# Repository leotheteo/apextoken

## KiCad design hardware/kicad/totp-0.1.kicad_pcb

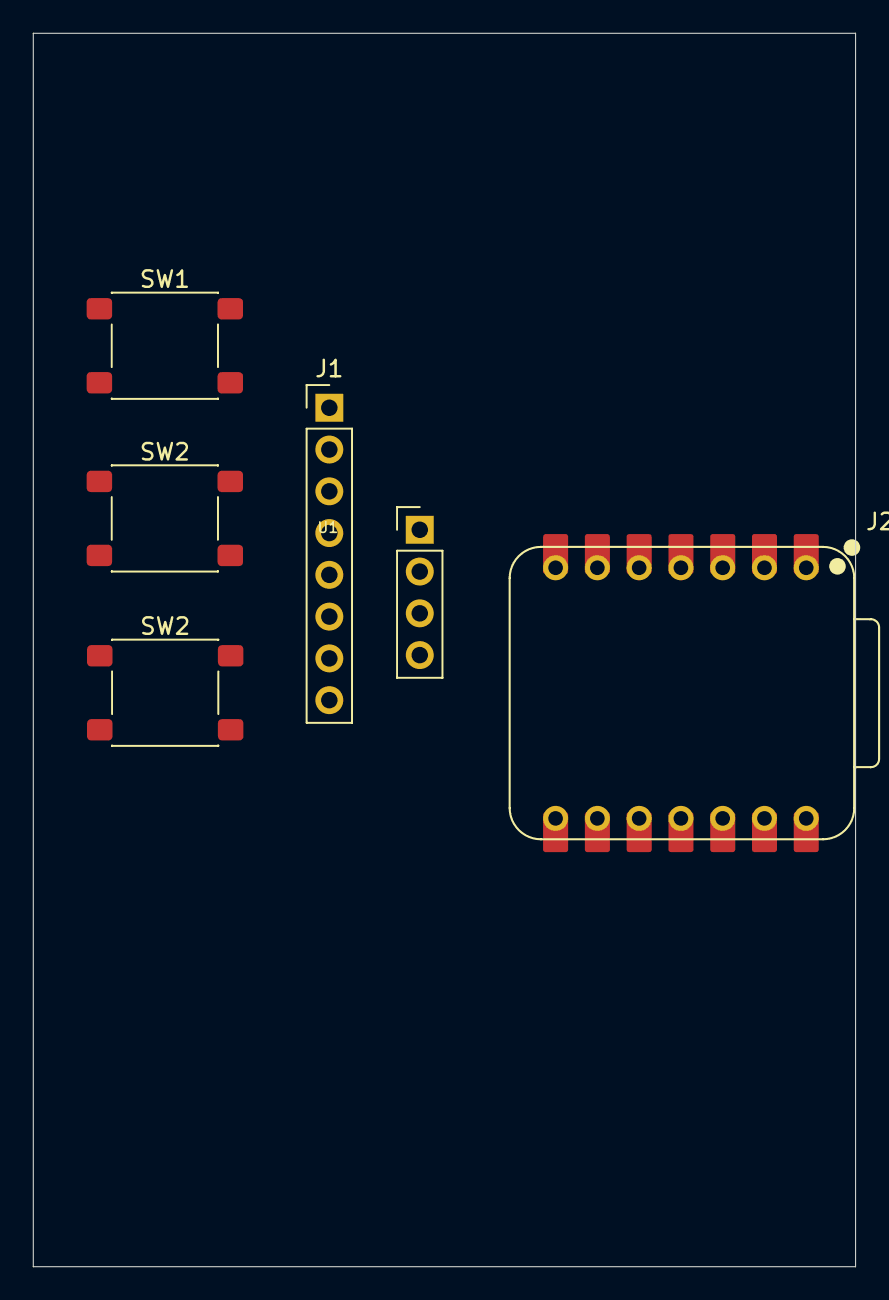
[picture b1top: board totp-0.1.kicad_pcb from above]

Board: 2 copper layers, 50.0 x 75.0 mm, 6 parts (0 on the bottom side), 13 nets, no tracks yet.

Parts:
J1: Conn_01x08; PinHeader_1x08_P2.54mm_Vertical
J2: Conn_01x04; PinHeader_1x04_P2.54mm_Vertical
SW1, SW2, SW2#2: SW_Push; SW_SPST_PTS645Sx43SMTR92
U1: XIAO-nRF52840-SMD; XIAO-nRF52840-DIP

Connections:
+3V3: J1.1, J2.2, U1.12 (3V3_OUT)
/BTN_CONFIRM: SW2.1, U1.10 (D9)
/BTN_NEXT: SW1.1, U1.7 (D6)
/BTN_PREV: SW2#2.1, U1.8 (D7)
/EPD_BUSY: J1.8, U1.1 (D0)
/EPD_CLK: J1.4, U1.9 (D8)
/EPD_CS: J1.5, U1.2 (D1)
/EPD_DC: J1.6, U1.3 (D2)
/EPD_DIN: J1.3, U1.11 (D10)
/EPD_RST: J1.7, U1.4 (D3)
/I2C_SCL: J2.4, U1.6 (D5)
/I2C_SDA: J2.3, U1.5 (D4)
GND: J1.2, J2.1, SW1.2, SW2.2, SW2#2.2, U1.13 (GND)
